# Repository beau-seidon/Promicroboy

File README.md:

# Arduinoboy (b_s)
~~Official~~ ArduinoBoy Repository for serial MIDI communication to the Nintendo Gameboy.

### The readme below is still based on the original repo, updates coming soon!
See changelog for more info.

## About
Arduinoboy is software for the [Arduino hardware platform](http://arduino.cc) that allows serial communication (MIDI) to the Nintendo Gameboy for music applications such as [LittleSoundDJ](http://littlesounddj.com), [Nanoloop.](http://www.nanoloop.com/), and [mGB](https://github.com/trash80/mGB)

## Current Features
* Affordable and easily accessible parts for assembly.
* Accurate MIDI Sync, Start and Stop commands.
* Push Button selector sets the sync/state modes [(7 modes available)](#modes-details)
* [mGB](https://github.com/trash80/mGB)
 Mode: Full MIDI in support across all Gameboy Channels, including a unique "poly" mode allows you to play your Game Boy like a synthesizer.
* Midi Out Doubles as a Midi Thru
* "Filtering" data for only sync messages, no dedicated MIDI line required.
* Can be powered by the Game Boy's gamelink port.
* USB upgradeable via Arduino.
* Midi settings configurable using a Mac/PC editor built in Max.
* Tested and works with DMG (Original), Gameboy Color, and Advance/SP.

## Modes Details
#### Mode 1 - LSDJ as MIDI Slave Sync
Slave your Game Boy running [LittleSoundDJ](http://littlesounddj.com) to your midi sequencer or Digital audio workstation.

You can send the arduinoboy midi notes to change sync resolution and start/stop the LSDJ sequencer.

_LSDJ Slave Mode Midi Note Effects:_

* 48 - `C-2` Sends a Sequencer Start Command
* 49 - `C#2` Sends a Sequencer Stop Command
* 50 - `D-2` Toggles Normal Tempo
* 51 - `D#2` Toggles 1/2 Tempo
* 52 - `E-2` Toggles 1/4 Tempo
* 53 - `F-2` Toggles 1/8 Tempo

Higher note values than these map LSDJ song position row offset on a Song Start.

In LSDJ the `sync` mode should be set to `Slave`

#### Mode 2 LSDJ as MIDI Master Sync.

Send Midi sync with LSDJ as a midi clock master, LSDJ also sends a Midi Note on message that corresponds to the song row number on play.

In LSDJ the `sync` mode should be set to `Master`

#### Mode 3 LSDJ PC Keyboard mode.
This mode emulates the [PC Keyboard Mode](http://littlesounddj.wikia.com/wiki/PC_Keyboard_Interface) built into LSDJ, allowing you to control the following aspects of LSDJ:

Features:

* The first octave controls M-U-T-E,
* Cursor control (LSDJ Live mode only),
* Table selection
* Table cue.

_PC Keyboard mode midi note map_

* 36 - `C-1` Mute Pu1 Off/On
* 37 - `C#1` Mute Pu2 Off/On
* 38 - `D-1` Mute Wav Off/On
* 39 - `D#1` Mute Noi Off/On
* 40 - `E-1` Livemode Cue Sequence
* 41 - `F-1` Livemode Cursor Up
* 42 - `F#1` Livemode Cursor Down
* 43 - `G-1` Livemode Cursor Left
* 44 - `G#1` Live mode Cursor Right
* 45 - `A-1` Table Up
* 46 - `A#1` Table Down
* 47 - `B-1` Cue Table
* 48+ - Notes from this note up will accept midi in from an external keyboard or sequencer and allow you to play the notes`C-2 to C-8`.
* Midi Program Change messages will select from instrument table
* Default Midi channel is 16. You can set this in the top of the main source file in the archive, or via the [Max Pat editor](#max).

In LSDJ the `sync` mode should be set to `Keyboard`

#### Mode 4 MIDI to Nanoloop sync
Sync [Nanoloop.](http://www.nanoloop.com/) to external midi clock signals sent to the midi in.

In Nanoloop, the sync mode should be set to `slave`.

#### Mode 5 Full MIDI with mGB
[mGB](https://github.com/trash80/mGB) is a Gameboy cartridge program (You need a Flash Cart and Transfer hardware) That enables the Gameboy to act as a MIDI supported sound module that allows full control of the Game Boy sound hardware.

It works with the old DMG Gameboy as well as GBC/GBA.

#### Mode 6 LSDJ MIDIMAP
Lsdj will sync to incoming MIDI sync, and incoming MIDI notes are mapped to LSDJ's song row #. The currently selected row's MIDI note is displayed on the top right of the LSDJ screen, and incoming MIDI notes will also display the relative song row number in the same location.

In LSDJ the `sync` mode should be set to `MI.MAP`.

*This requires a special version of LSDJ, which can be found in your account on the [LSDJ website](http://littlesounddj.com/lsd/latest/full_version/).*

#### Mode 7 LSDJ MIDIOUT
Each of the 4 gameboy channels send MIDI data on 4 midi channels by the use of effects commands:

* `Nxx` - Sends a MIDI Note - Absolute to the value placed in the effect. N00 sends note off, `N01`-`N6F` send midi notes 1 to 112.
* `Qxx` - Sends a [MIDI Note](http://www.electronics.dit.ie/staff/tscarff/Music_technology/midi/midi_note_numbers_for_octaves.htm) relative to the current channel's pitch. The effect value is a offset. so `Q0C` in `PU1` would send a note 1 octave higher than what `PU1` is currently playing. This is useful as a table command to track midi notes as normal notes in the sequencer.
* `Xxx` - Sends a MIDI CC - By default in Arduinoboy the high nibble selects a CC#, and the low nibble sends a value `0-F` to `0-127`. This can be changed to allow just 1 midi CC with a range of `00`-`6F`, or 7 CCs with scaled or unscaled values.
* `Yxx` - Sends a program/patch/preset change.

By default each channel of LSDJ is mapped to midi channels 1-4. For example note commands from PU1 will be sent to midi channel 1.

In LSDJ the `sync` mode should be set to `Midiout`.

*This requires a special version of LSDJ, which can be found in your account on the [LSDJ website](http://littlesounddj.com/lsd/latest/full_version/).*

## Max Editor

[The Arduinoboy Editor for Max](https://github.com/trash80/Arduinoboy/tree/master/Editor) for PC/OSX machines is a gui editor that allows you to edit the various global midi settings of your arduinoboy without editing or flashing code, over midi. It used to required the now deprecated Max Runtime, but you can also run it using a demo of [Cycling '74's Max application](https://cycling74.com/downloads/)

### Maxpat Settings
* `Midi In/Out`
Connect your arduinoboy to these ports on your system. Once it has connected, all the lights on your arduinoboy should flash in order, and the editor will show a green `Connected`.
* `Mode`
Setting this will tell your arduinoboy what mode to boot into automatically. This is handy if you built your own arduinoboy and decided you wanted to skimp out on LEDs and a button.
* `LSDJ Slave Mode settings` - The midi channel LSDJ slave mode will receive its commands on.
* `LSDJ Master Mode settings` - The midi channel LSDJ Master mode will send its midi notes mapped to row number on.
* `Keyboard Mode settings` - What channel LSDJ will look for its keyboard mode midi commands. No idea what compatibility mode does.
* `mGB midi settings` - Map each incoming midi channel to a specific Gameboy channel in mGB.
* `LSDJ Livesync/Livemap settings` - The midi channel Livesync/Livemap will listen to incoming midi commands from.
* `LSDJ Midiout settings` - Here you can set the following:
	* `Note midi channel` -  The channel each LSDJ channel will send it's midi note commands on.
	* `CC midi channel` -  The channel each LSDJ channel will send it's Continuous Controller commands on.
	* `CC 0` - The initial CC each channel will send. The type of data it will send is based on the next setting.
	* `CC Mode` - Game Boys have limitations! You can either have arduinoboy send one CC with many values, or 7 with limited 8bit values. By default in Arduinoboy the high nibble selects a CC#, and the low nibble sends a value [0-F] to [0-127]. This can be changed to allow just 1 midi CC with a range of 00-6F, or 7 CCs with scaled or unscaled values.
	* `CC Scaling ` - Set wether the 7 CCs are scaled or unscaled.

## Future Features & wishlist
  * Build instructions, and a Arduino Shield

## How To build an Arduinoboy

* [Build Photos](http://flickr.com/photos/trash80/2316803175/in/set-72157604068871573/)
* [Old version (Pre 1.1.0)](http://trash80.net/junkfood/arduinoboy/arduinoboy-schem-v.0.9.8-r1.png)

### Video Demos

  * [Keyboard Mode Test](http://youtube.com/watch?v=TnLUuvc78XY)
  * [Sync Demos](http://youtube.com/watch?v=iVmhy-Lo7BI)
  * [Arduino inside of Gameboy DMG](http://youtube.com/watch?v=VwrMuOA0VnY)
  * [mGB Example & Arduinoboy build into a DMG](http://vimeo.com/1853931)
  * [PDF explores mGB with a MIDI guitar](http://www.youtube.com/watch?v=HAU9MzZ2qeE)

## Thanks To
  * [Arduino](http://arduino.cc)
  * [Nitro2k01](http://blog.gg8.se/wordpress/) for ASM help with mGB
  * [GWEM](http://www.preromanbritain.com/gwem/lsdj_midi/g33k.html) g33k page
  * [Midines](http://wayfar.net) Thanks for the help x|k!
  * [firestARTer](http://www.firestarter-music.de) help with keyboard & Midi handling information.
  * [Gijs Gieskes](http://gieskes.nl) Found source code that gave insight into Nanoloop sync
  * [Little Sound DJ](http://littlesounddj.com)
  * [http://devrs.com/gb](http://devrs.com/gb) Madcatz PC link port for gb serial specs
  * [http://chipmusic.org](http://chipmusic.org) For all things Chipmusic.

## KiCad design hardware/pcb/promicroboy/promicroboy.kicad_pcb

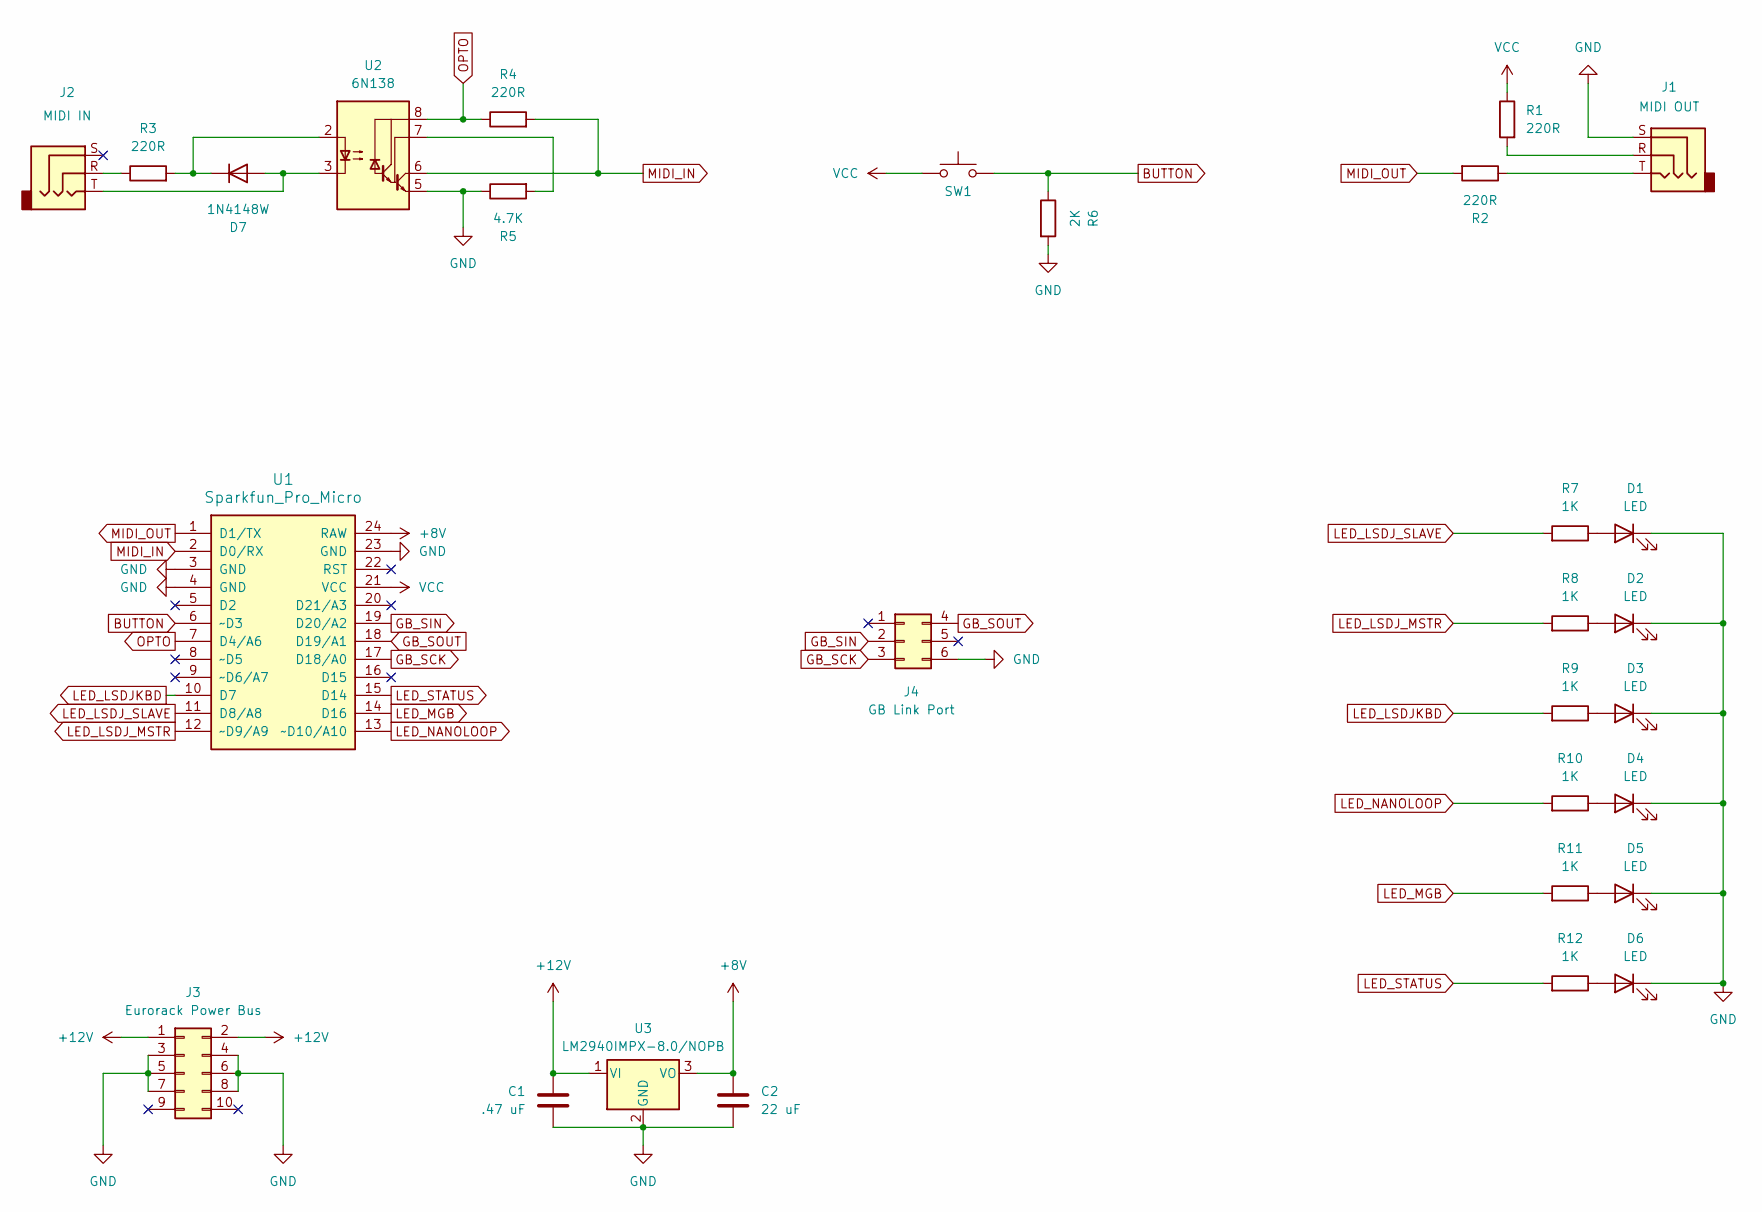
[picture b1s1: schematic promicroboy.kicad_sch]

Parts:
C1: .47 uF; C_0805_2012Metric_Pad1.18x1.45mm_HandSolder
C2: 22 uF; C_1206_3216Metric_Pad1.33x1.80mm_HandSolder
D1, D2, D3, D4, D5, D6: LED; LED_D3.0mm
D7: 1N4148W; D_SOD-123
J1: MIDI OUT; Jack_3.5mm_QingPu_WQP-PJ398SM_Vertical_CircularHoles_TRS
J2: MIDI IN; Jack_3.5mm_QingPu_WQP-PJ398SM_Vertical_CircularHoles_TRS
J3: Eurorack Power Bus; PinHeader_2x05_P2.54mm_Vertical
J4: GB Link Port; PinSocket_1x06_P2.54mm_Vertical
R1, R2, R3, R4: 220R; R_0805_2012Metric_Pad1.20x1.40mm_HandSolder
R5: 4.7K; R_0805_2012Metric_Pad1.20x1.40mm_HandSolder
R6: 2K; R_0805_2012Metric_Pad1.20x1.40mm_HandSolder
R7, R8, R9, R10, R11, R12: 1K; R_0805_2012Metric_Pad1.20x1.40mm_HandSolder
SW1: SW_Push; SW_PUSH_6mm
U1: Sparkfun_Pro_Micro
U2: 6N138; DIP-8_W7.62mm_Socket
U3: LM2940IMPX-8.0/NOPB; SOT-223-3_TabPin2

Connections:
+8V: C2.1, U1.24 (RAW), U3.3 (VO)
+12V: C1.1, J3.1, J3.2, U3.1 (VI)
BUTTON: R6.1, SW1.1, U1.6 (~D3)
GB_SCK: J4.3 (SCK), U1.17 (D18/A0)
GB_SIN: J4.2 (SIN), U1.19 (D20/A2)
GB_SOUT: J4.4 (SOUT), U1.18 (D19/A1)
GND: C1.2, C2.2, D1.1 (K), D2.1 (K), D3.1 (K), D4.1 (K), D5.1 (K), D6.1 (K), J1.S, J3.3, J3.4, J3.5, J3.6, J3.7, J3.8, J4.6 (GND), R5.1, R6.2, U1.3 (GND), U1.4 (GND), U1.23 (GND), U2.5 (GND), U3.2 (GND)
LED_LSDJKBD: R9.2, U1.10 (D7)
LED_LSDJ_MSTR: R8.2, U1.12 (~D9/A9)
LED_LSDJ_SLAVE: R7.2, U1.11 (D8/A8)
LED_MGB: R11.2, U1.14 (D16)
LED_NANOLOOP: R10.2, U1.13 (~D10/A10)
LED_STATUS: R12.2, U1.15 (D14)
MIDI_IN: R4.2, U1.2 (D0/RX), U2.6 (VO2)
MIDI_OUT: R2.2, U1.1 (D1/TX)
unnamed: D1.2 (A), R7.1
unnamed: D2.2 (A), R8.1
unnamed: D3.2 (A), R9.1
unnamed: D4.2 (A), R10.1
unnamed: D5.2 (A), R11.1
unnamed: D6.2 (A), R12.1
unnamed: D7.2 (A), J2.T, U2.3 (C2)
unnamed: D7.1 (K), R3.2, U2.2 (C1)
unnamed: J1.R, R1.2
unnamed: J1.T, R2.1
unnamed: J2.R, R3.1
unnamed: R5.2, U2.7 (VO1)
OPTO: R4.1, U1.7 (D4/A6), U2.8 (VCC)
VCC: R1.1, SW1.2, U1.21 (VCC)

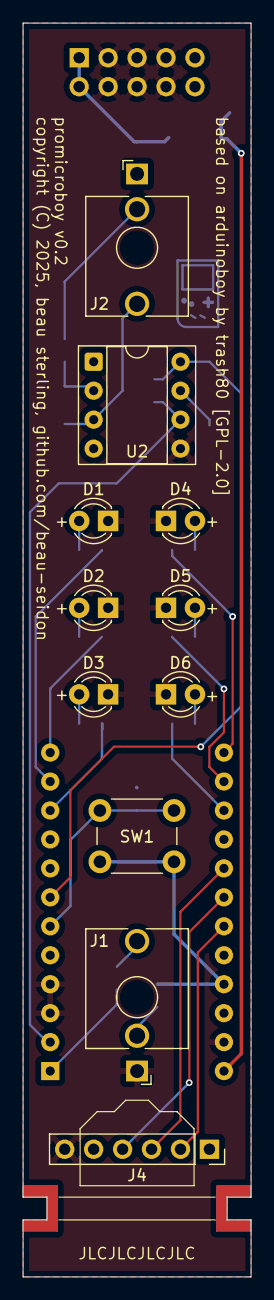
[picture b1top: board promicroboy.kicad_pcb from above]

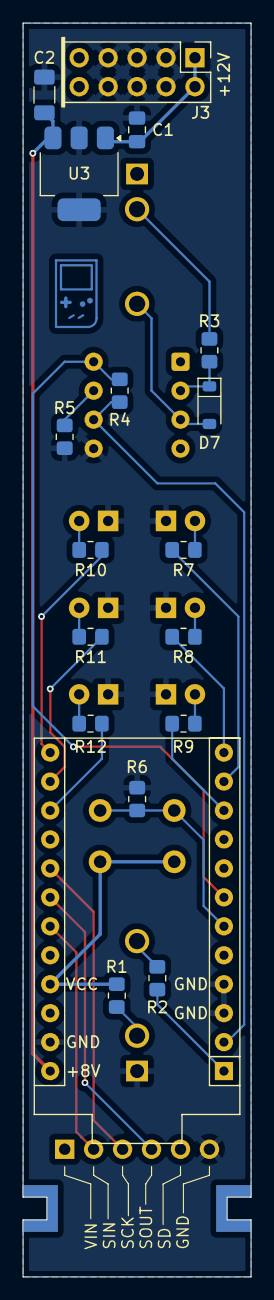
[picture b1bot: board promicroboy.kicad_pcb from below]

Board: 2 copper layers, 20.0 x 110.0 mm, 29 parts (18 on the bottom side), 29 nets.

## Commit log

2025-09-01 WIP: big overhaul. Created Promicroboy! rearraged, refactored, manual merges etc.
    see changelog.md
2025-09-01 added build photos
2026-03-26 it compiles! completed manual merge / refactor of tstirrat and Chiptune-Anamnesis repo's (finally). also more code cleanup and consistency fixes. next commit will be bug fixes...
2026-03-28 improved mode switching so it doesn't lag or get stuck anymore. also a little more code cleanup.

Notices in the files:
hardware/pcb/promicroboy/promicroboy.kicad_pcb:
Copyright (C) 2025, Beau Sterling, github.com/beau-seidon
based on arduinoboy by trash80 [GPL-2.0]
